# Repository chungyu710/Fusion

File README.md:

# Fusion
Capstone Design Project

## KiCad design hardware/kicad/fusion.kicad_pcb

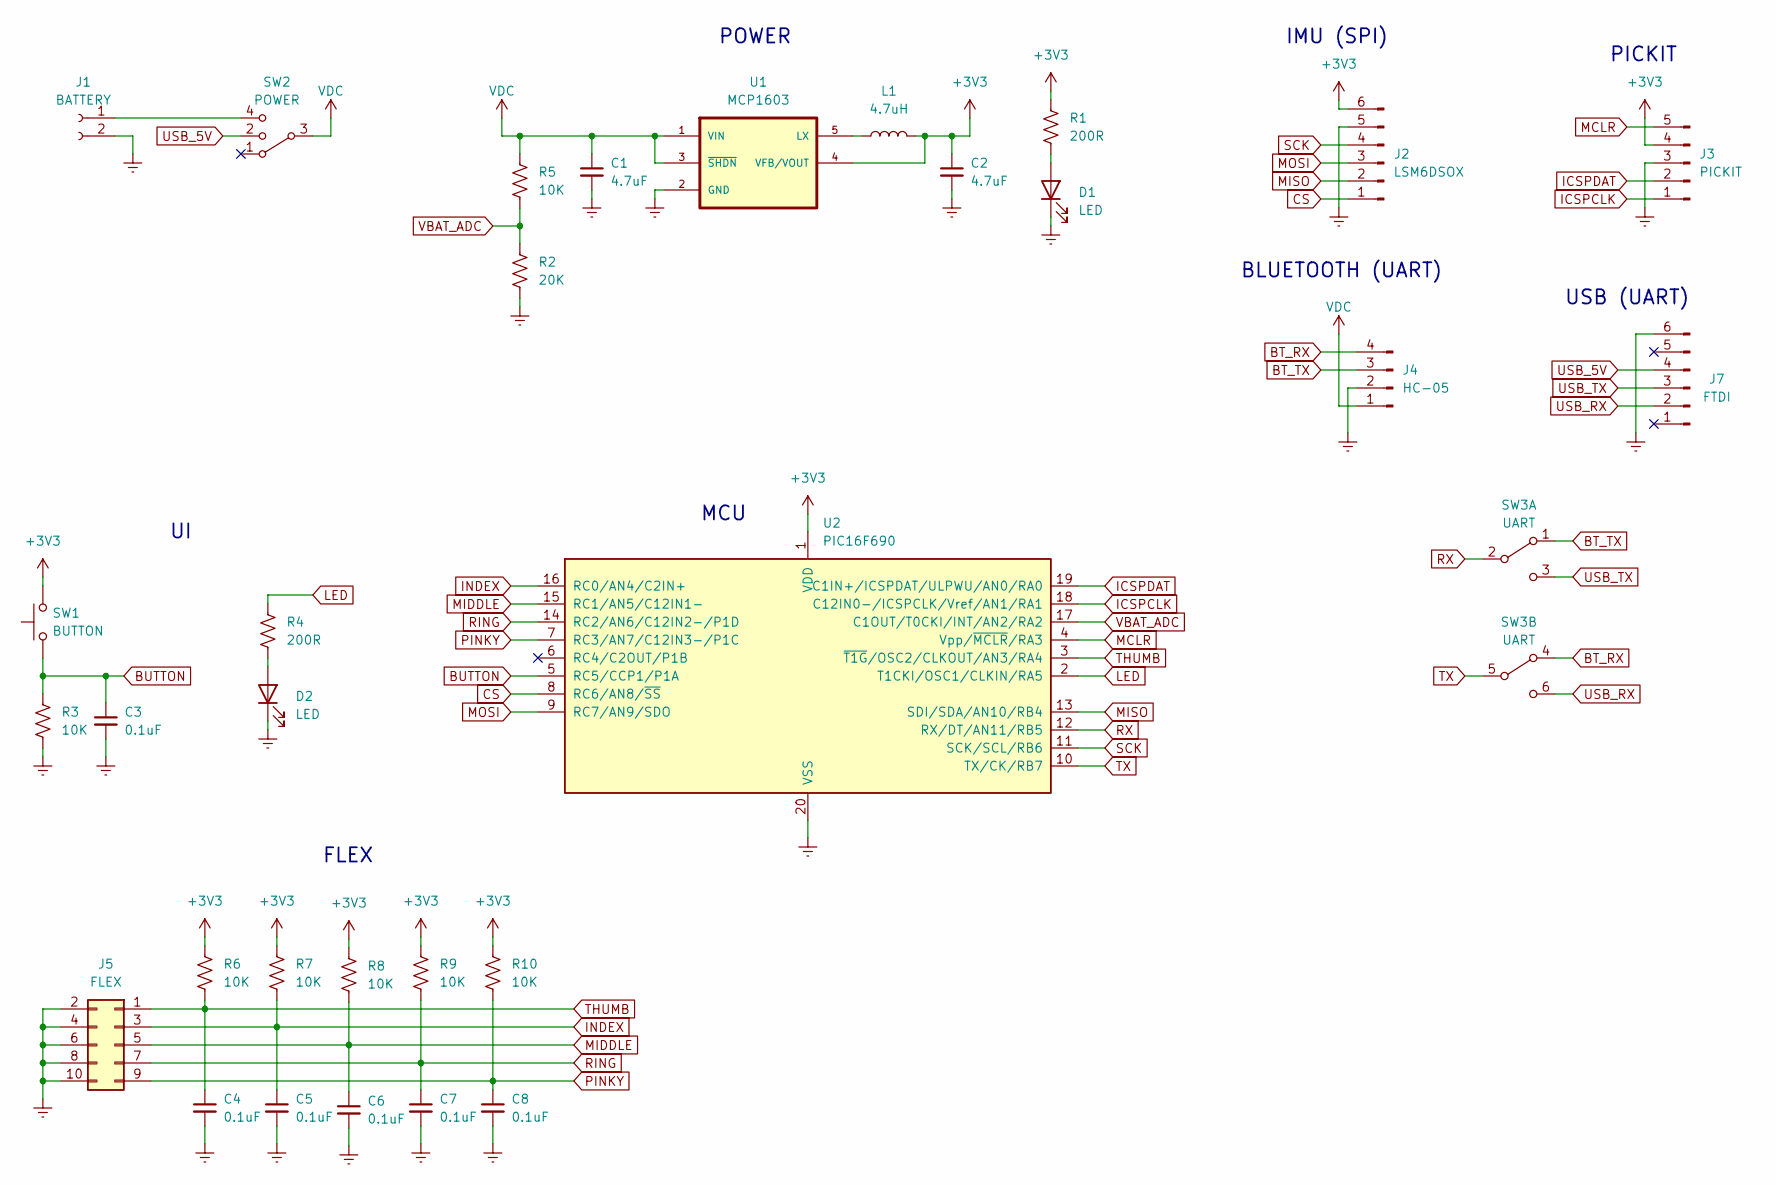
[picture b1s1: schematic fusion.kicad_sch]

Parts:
C1, C2: 4.7uF; C_0603_1608Metric_Pad1.08x0.95mm_HandSolder
C3, C4, C5, C6, C7, C8: 0.1uF; C_0603_1608Metric_Pad1.08x0.95mm_HandSolder
D1, D2: LED; LED_0603_1608Metric_Pad1.05x0.95mm_HandSolder
J1: BATTERY; JST
J2: LSM6DSOX; PinHeader_1x06_P2.54mm_Horizontal
J3: PICKIT; PinSocket_1x05_P2.54mm_Vertical
J4: HC-05; PinHeader_1x04_P2.54mm_Horizontal
J5: FLEX; PinHeader_2x05_P2.54mm_Horizontal
J7: FTDI; PinSocket_1x06_P2.54mm_Vertical
L1: 4.7uH; L_0603_1608Metric_Pad1.05x0.95mm_HandSolder
R1, R4: 200R; R_0603_1608Metric_Pad0.98x0.95mm_HandSolder
R2: 20K; R_0603_1608Metric_Pad0.98x0.95mm_HandSolder
R3, R5, R6, R7, R8, R9, R10: 10K; R_0603_1608Metric_Pad0.98x0.95mm_HandSolder
SW1: BUTTON; SW_PUSH_6mm_H5mm
SW2: POWER; SP3T
SW3: UART; SPDT
U1: MCP1603; TSOT-23-5_HandSoldering; MPN MCP1603T-330I/OS
U2: PIC16F690; DIP-20_W7.62mm_Socket

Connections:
+3V3: C2.1, J2.6, J3.4, L1.2, R1.2, R6.1, R7.1, R8.1, R9.1, R10.1, SW1.2, U1.4 (VFB/VOUT), U2.1 (VDD)
BT_RX: J4.4, SW3.4 (A)
BT_TX: J4.3, SW3.1 (A)
BUTTON: C3.1, R3.1, SW1.1, U2.5 (RC5/CCP1/P1A)
CS: J2.1, U2.8 (RC6/AN8/~SS)
GNDREF: C1.2, C2.2, C3.2, C4.2, C5.2, C6.2, C7.2, C8.2, D1.1 (K), D2.1 (K), J1.2, J2.5, J3.3, J4.2, J5.2, J5.4, J5.6, J5.8, J5.10, J7.6, R2.2, R3.2, U1.2 (GND), U2.20 (VSS)
ICSPCLK: J3.1, U2.18 (C12IN0-/ICSPCLK/Vref/AN1/RA1)
ICSPDAT: J3.2, U2.19 (C1IN+/ICSPDAT/ULPWU/AN0/RA0)
INDEX: C5.1, J5.3, R7.2, U2.16 (RC0/AN4/C2IN+)
LED: R4.2, U2.2 (T1CKI/OSC1/CLKIN/RA5)
MCLR: J3.5, U2.4 (Vpp/~MCLR/RA3)
MIDDLE: C6.1, J5.5, R8.2, U2.15 (RC1/AN5/C12IN1-)
MISO: J2.2, U2.13 (SDI/SDA/AN10/RB4)
MOSI: J2.3, U2.9 (RC7/AN9/SDO)
unnamed: D1.2 (A), R1.1
unnamed: D2.2 (A), R4.1
unnamed: J1.1, SW2.4
unnamed: L1.1, U1.5 (LX)
PINKY: C8.1, J5.9, R10.2, U2.7 (RC3/AN7/C12IN3-/P1C)
RING: C7.1, J5.7, R9.2, U2.14 (RC2/AN6/C12IN2-/P1D)
RX: SW3.2 (B), U2.12 (RX/DT/AN11/RB5)
SCK: J2.4, U2.11 (SCK/SCL/RB6)
THUMB: C4.1, J5.1, R6.2, U2.3 (~T1G/OSC2/CLKOUT/AN3/RA4)
TX: SW3.5 (B), U2.10 (TX/CK/RB7)
USB_5V: J7.4, SW2.2
USB_RX: J7.2, SW3.6 (C)
USB_TX: J7.3, SW3.3 (C)
VBAT_ADC: R2.1, R5.2, U2.17 (C1OUT/T0CKI/INT/AN2/RA2)
VDC: C1.1, J4.1, R5.1, SW2.3, U1.1 (VIN), U1.3 (~SHDN)

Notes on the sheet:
IMU (SPI)
MCU
FLEX
BLUETOOTH (UART)
PICKIT
USB (UART)
POWER

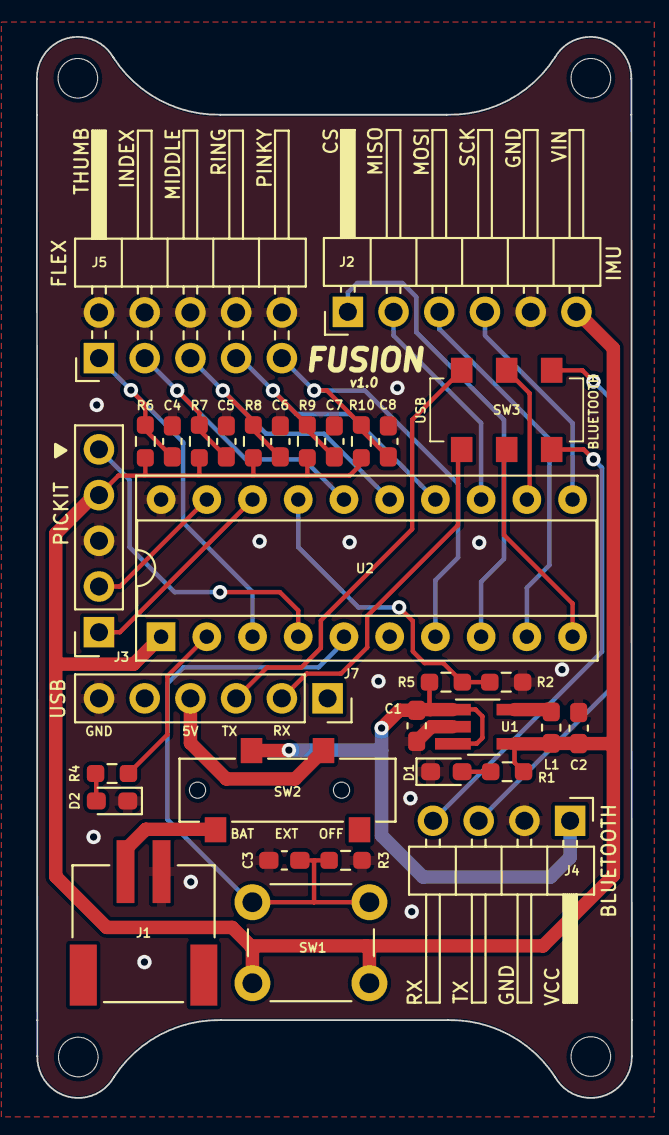
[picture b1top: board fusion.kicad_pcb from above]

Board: 2 copper layers, 33.0 x 58.9 mm, 32 parts (0 on the bottom side), 29 nets.

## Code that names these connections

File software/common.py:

# Commands:
PING = "\x00"
SENSORS_ALL = "\x30"
SENSOR_ACCELEROMETER = "\x31"

class Sensors:
    def __init__(self, accel_data, gyro_data, flex_data):
        self.accel_data = accel_data
        self.gyro_data =  gyro_data
        self.flex_data = flex_data

    def __str__(self):
        return str(self.accel_data) + str(self.gyro_data) + str(self.flex_data)

class Accelerometer:
    def __init__(self, x, y, z):
        self.x = x
        self.y =  y
        self.z = z

    def __str__(self):
        return "Accelerometer values: " + " (x, y, z): (" + str(self.x) + ", " + str(self.y) + ", " +  str(self.z) + ")\n"

class Gyro:
    def __init__(self, pitch, yaw, roll):
        self.roll = roll
        self.pitch =  pitch
        self.yaw = yaw

    def __str__(self):
        return "Gyro values: " + " (roll, pitch, yaw): (" + str(self.roll) + ", " + str(self.pitch) + ", " +  str(self.yaw) + ")\n"


class Flex:
    def __init__(self, thumb, index, middle, ring, pinky):
        self.thumb = thumb
        self.index =  index
        self.middle = middle
        self.ring = ring
        self.pinky = pinky

    def __str__(self):
        return "Flex sensor values: " + " (thumb, index, middle, ring, pinky): (" + str(self.thumb) + ", " + str(self.index) + ", " +  str(self.middle) + ", " + str(self.ring) + ", " +  str(self.pinky) + ")\n"

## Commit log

2022-05-30 Top-level .gitignore
2022-05-30 Hello world LED blink on 3V3
2022-06-01 Adapt generalized Makefile to work with XC8
2022-06-01 Folders and gitignores for hardware and software
2022-06-02 System startup code with LED flash
2022-06-02 Cleanup and comments
2022-06-02 Reorder init calls
2022-06-08 README for how to install the XC8 compiler on linux
2022-06-09 Comments
2022-06-09 System initialization and LED (#1)
    - Reset all ports to digital outputs
    - Set oscillator frequency to 8 MHz (max speed)
    - Blink LED 3 times as a startup indicator
    - LED API
2022-06-09 Fix Makefile bug for moving artifact
2022-06-09 Fixed width integer types
2022-06-09 Define APIs for PIC hardware peripherals
2022-06-09 Define APIs for drivers
2022-06-09 Revive the LED blink test
2022-06-09 More README information
2022-06-09 Datasheets for MCU, buck, and IMU
2022-06-09 Power voltage return type (mV)
2022-06-09 Rename power to battery
2022-06-09 Generate KiCad project files
2022-06-10 KiCad project settings
2022-06-10 Regenerate project
2022-06-10 Add MCP1603 buck symbol
2022-06-10 Make buck symbol less ugly
2022-06-10 Power system schematic
2022-06-10 IMU SPI header
2022-06-10 Rest of schematic
2022-06-12 Connect PIC pin to EN/KEY for BT instead of STATE
2022-06-13 System initialization cleanup
2022-06-14 Change battery monitor resistors to handle 5 V with less leakage
2022-06-14 Labels for switches
2022-06-14 Remove old version of buck symbol library
2022-06-15 Split IMU drivers into accel and gyro
2022-06-15 More modular system initialization
2022-06-15 Empty source code files and fix syntax errors
2022-06-15 Potential header
2022-06-15 more stuff
2022-06-15 More setup stuff
2022-06-15 Note on include paths
2022-06-15 Test renaming
2022-06-15 Makefile printing
2022-06-16 Remove sequence and add more commands
2022-06-16 Rework commands
2022-06-17 Reset command
2022-06-17 enum naming
2022-06-17 compile error
2022-06-17 chung's changes
2022-06-20 how to use IPECMD
2022-06-22 macro rename
2022-06-22 Explicit enum values
2022-06-22 more enum naming
2022-06-22 updated hardware gitignore
2022-06-24 [TEMP] 115200 bps baud rate
2022-06-24 SPI working (read and write)
2022-06-24 SPI API for buffered reading and writing
2022-06-24 Dynamically set accel range
2022-06-24 Read all accel axes with one SPI command
2022-06-24 Read X acceleration
2022-06-24 Multi-byte read/write for IMU over SPI
2022-06-24 Read accel X with multi byte SPI read command
2022-06-24 Read gyro and reorder struct for continuous read
2022-06-24 IMU drivers for reading and writing registers
2022-06-24 Dynamic gyro range
2022-06-24 cleanup
2022-06-24 Test for endianness (it's little endian btw)
2022-06-24 Wrappers for reading and writing single IMU register
2022-06-27 Select some footprints
2022-06-27 0603 footprints and SP3T
2022-06-29 Placing components
2022-06-30 Moving around components
2022-07-03 Models and footprints for JST and switches
2022-07-03 Route board
2022-07-04 Properly link 3D models
2022-07-04 Rounded corners, mounting holes, and DRC
2022-07-05 PCB cleanup and branding
2022-07-05 Remove unnecessary PIC16F690 headers
2022-07-05 Enable brownout reset to stabilize power-on reset
    PC was not being reset on power up.
2022-07-06 add code for calibration processor
2022-07-06 add code for state lookup and json file
2022-07-06 update comments
2022-07-06 don't use global var
2022-07-06 change filepath used in get_states_from_json
2022-07-06 added uart tx/rx functionality
2022-07-06 formatting changes
2022-07-06 more formatting changes
2022-07-06 Switch to final UART drivers
2022-07-07 Rename FTDI to USB
2022-07-07 Power HC-05 from raw power source
    BT module has an LDO that requires at least 3V6.
    Powering from 3V3 causes improper regulation and
    browns out the entire system.
2022-07-07 Better ground stitching and silk fix for power switch
2022-07-07 Change LED resistors to 200R (DigiKey availability)
2022-07-07 LED blink forever
    Useful for errors
2022-07-07 Datasheets and docs for usb-ttl
2022-07-08 Implement Chung's feedback for PCB
2022-07-08 small routing changes
2022-07-12 Silence unused function warning
2022-07-12 Some constants for ADC
2022-07-12 WIP service
2022-07-12 Compiler manual
2022-07-12 Don't create artifacts folder on make clean
2022-07-12 Switch LED resistors to 220R as per DigiKey availability
2022-07-12 initial deserializer code
2022-07-12 added agent with mouse movements(pass in acceleration values)
2022-07-12 deserializer almost done
2022-07-14 changed state lookup to use class
2022-07-14 progress
2022-07-14 good for demo
2022-07-15 Deserializer cleanup
2022-07-15 velocity testing and mouse with gyro
2022-07-15 Control mouse with gyro
2022-07-15 Use advanced logging API
2022-07-15 cleanup and colours
2022-07-17 Clean up main
2022-07-17 Basic sensor reading (no flex)
2022-07-17 Change LED pin to match PCB
2022-07-17 Link response with checksum over payload and header
2022-07-17 Dynamic sizeof
2022-07-17 Service firmware (reset not implemented)
2022-07-17 Sample testing script
2022-07-17 Measure latency and switch mouse axes
2022-07-17 Enable actual service
2022-07-18 fifo working but slow
2022-07-18 Abort with blinking LED forever
    - also included dummy flex data
2022-07-18 RX overrun detection
2022-07-18 Reset using watchdog and run service in interrupt
2022-07-18 Button firmware
2022-07-18 Dummy battery firmware
2022-07-18 cleanup and finish initializing drivers
2022-07-18 Send button with sensors
2022-07-18 Parse button in deserializer
2022-07-18 Battery command testing
2022-07-18 Check if IMU is online
2022-07-18 Press button to reboot during an abort
2022-07-18 Change battery undervolt threshold to 3V6 for HC-05 LDO
2022-07-21 Stack print sensors
2023-01-22 add code for flex sensors
2023-01-24 added flex sensor adc code
2023-01-27 Read battery voltage and detect undervolting
2023-01-27 Fix IMU whoami check
2023-01-27 Reboot after pressing button during abort
2023-01-27 Pack structs
2023-01-27 RX queue
2023-01-27 Power sequencing delay for IMU initialization
2023-01-27 RX queue and move service out of ISR
2023-01-27 Check for low battery on boot
2023-01-27 Abort reason and fix GIE race condition
2023-01-27 Remove battery check on startup (not reliable)
2023-01-27 Periodic battery voltage check
2023-01-27 Debounce low battery voltage on boot
2023-01-29 firmware got messed up
2023-01-31 Remove RX queue and abort caller message
    - RX queue is prone to overflow and since
    only one packet in flight it is not required.
2023-01-31 Streaming infrastructure
2023-02-14 added calibration script; good enough for initial demo?
2023-02-19 Clean up protocol python code
2023-02-19 More cleanup
2023-02-19 ping and reset on startup
2023-02-19 verify checksum on ping and reset
2023-02-19 Somewhat working stream
2023-02-19 Fix sample
2023-02-19 Rename response to Header
    - response is header + payload
2023-02-19 remove printf
2023-02-19 status and checksum checks
2023-02-19 minor changes
2023-02-19 Rename sensors command to sample
2023-02-19 rename some stuff
2023-02-19 copy sample.py
2023-02-19 Burst working with polling
2023-02-20 abort macros
2023-02-20 Internalize serial handle and kinda fast burst
2023-02-20 Remove RX queue (again)
2023-02-20 More burst stuff
2023-02-20 single threaded consistent
2023-02-20 fusion is faster but messed up
2023-02-20 Reduce wireless latency using burst mode
2023-02-20 clean up sample and burst
2023-02-20 proper debug levels
2023-02-20 Remove all streaming code
2023-02-20 Mouse smoothing
2023-02-20 Move some files around
2023-02-20 Move battery check code
2023-02-20 Move service to link
2023-02-20 Change undervolt to 3.3 V
2023-02-20 battery voltage test script
2023-02-20 deadzone
2023-02-20 serial port dump script
2023-02-21 log level command line parameter
2023-02-21 Command line arguments for hand and mode
2023-02-21 Reprint battery voltage
2023-02-21 Calibration left hand ring finger
2023-02-21 Latency calculation command line flag
2023-02-22 Rename artifacts folder
2023-02-22 UVLO
2023-02-22 Fix out of scope variable
2023-02-22 Send battery low voltage when entering UVLO
2023-02-22 Revert undervolt back to 3.4 V
2023-02-22 Enumerate deserializer constants
2023-02-23 Stabilize purge
2023-02-23 idek anymore
2023-02-23 alt gestures
2023-02-23 secret exit gesture
2023-02-23 latency print
2023-02-23 prints
2023-03-03 updated calibrate file
2023-03-03 works on windows
2023-03-03 fixed single click mode
2023-03-03 sensitivity and deadzone tuning
2023-03-03 added a scale variable
2023-03-03 Easter egg
2023-03-03 Add back --port argument
2023-03-03 Revert "Easter egg"
    This reverts commit deea70c4c1628a4b67211d04470c2c8752b901dd.
2023-03-04 Put back --port args in battery.py
2023-03-12 fix battery print
2023-03-12 fix burst race condition
2023-03-12 fixed bugs
2023-03-14 Fixed ring sensor
2023-03-14 fixed ring
